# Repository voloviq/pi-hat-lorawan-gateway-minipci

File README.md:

# pi-hat-lorawan-gateway-minipci
Pi Hat with mini pci express connector for lorawan gateway rk833

PCB View

This is first prototype version and can have some connection mistakes. Please check it before use!.

This update was made in lates KiCad version 5.99.

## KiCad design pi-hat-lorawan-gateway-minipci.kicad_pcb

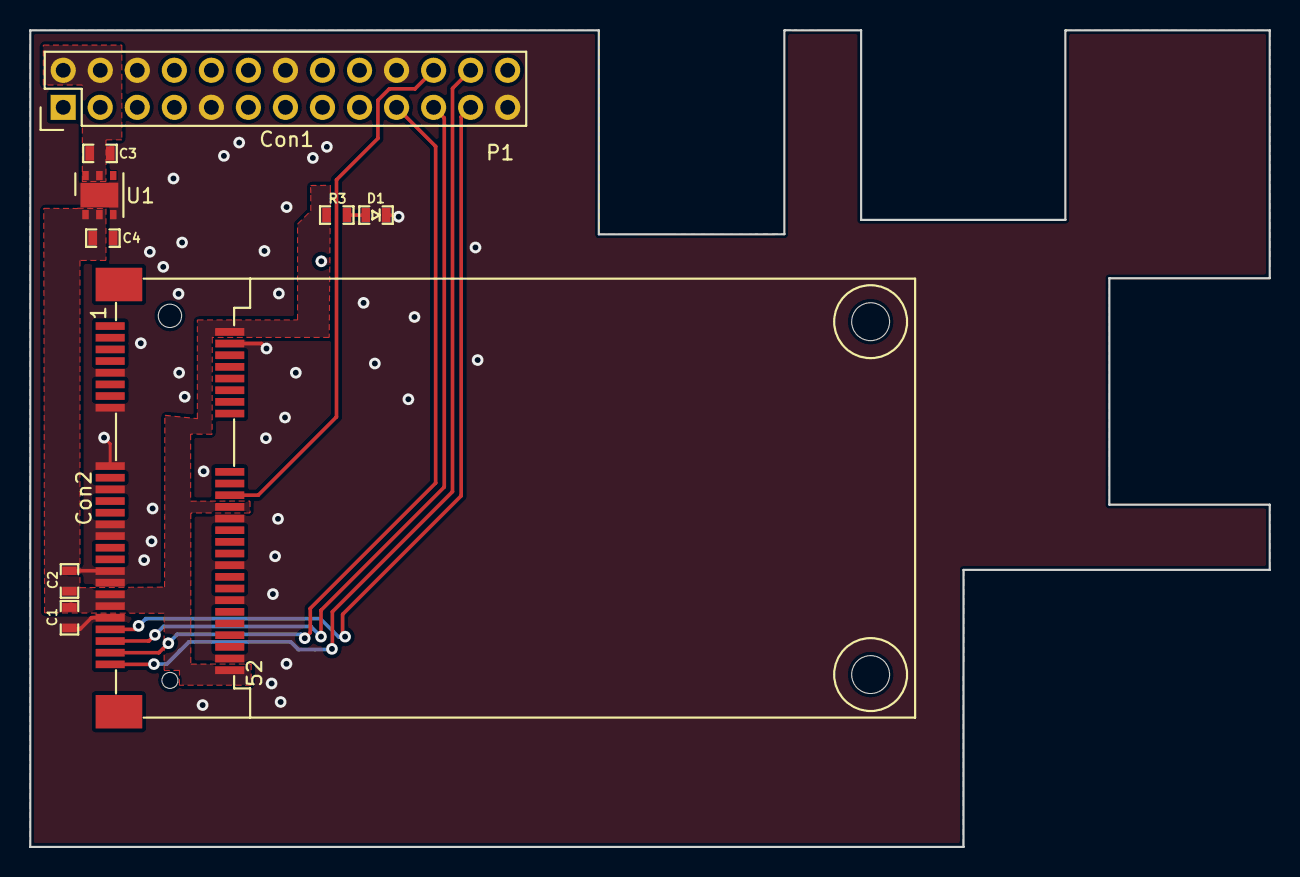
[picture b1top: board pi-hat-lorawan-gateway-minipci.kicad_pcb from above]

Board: 2 copper layers, 85.0 x 56.0 mm, 9 parts (0 on the bottom side), 9 nets.

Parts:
C1: 100n; 100nF_0603
C2, C3, C4: 10uF; 10uF_10V_0603
Con1: RPi-Header-2x13; Header_Socket_2x13x2_54mm
Con2: 2041119-1
D1: KPG-1608SURKC-T; LED_KPG-1608SURKC-T
R3: 200R; 200R_0603
U1: LD39200; LD39200PU33R

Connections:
3V3: C1.1, C2.1, C4.1, Con2.2, Con2.24, Con2.39, Con2.41, Con2.52, R3.2, U1.1 (VOUT), U1.2 (ADJ/SENSE)
5V: C3.1, Con1.2, Con1.4, U1.5 (EN), U1.6 (VIN)
/GPIO8(CE0): Con1.24, Con2.51
/GPIO9(MISO): Con1.21, Con2.47
/GPIO10(MOSI): Con1.19, Con2.49
/GPIO11(SCLK): Con1.23, Con2.45
/GPIO25: Con1.22, Con2.22
GND: C1.2, C2.2, C3.2, C4.2, Con1.6, Con1.9, Con1.14, Con1.20, Con1.25, Con2.4, Con2.9, Con2.15, Con2.17, Con2.21, Con2.26, Con2.27, Con2.29, Con2.34, Con2.35, Con2.37, Con2.40, Con2.43, Con2.50, D1.2 (K), U1.3 (GND), U1.EP
unnamed: D1.1 (A), R3.1

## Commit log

2021-01-21 Initial
2021-01-21 Finalized project and generated all production files
2021-02-18 Applied Issue 1, performed valid SPI connection to RPi
2021-02-18 Updated README.md and 3D view picture
2021-02-19 Added documentation
2021-03-16 Board revorked to RPI-4 Hat Vertical
2021-03-16 Added new model 3D in README.md file
2021-04-01 Applied issue and regenerated gerbers
2021-04-01 Applied issue, regenerated gerbers
